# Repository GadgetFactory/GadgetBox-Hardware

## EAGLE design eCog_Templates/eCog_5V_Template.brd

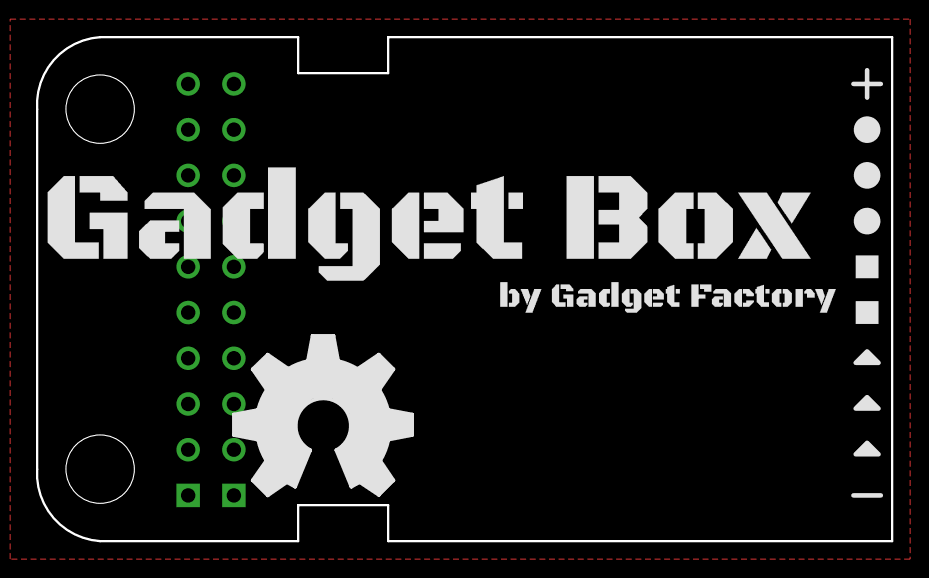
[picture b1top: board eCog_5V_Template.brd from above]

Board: 2 copper layers, 47.5 x 28.0 mm, 11 parts (0 on the bottom side), 2 nets, no tracks yet.

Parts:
ECOG: ECOG_DUALTHROUGHHOLE; ECOG_DUAL_TH
U$1: GADGETBOX_TEXT
U$2, U$3, U$4: LEGEND_DIO
U$5, U$6: LEGEND_PWM
U$7, U$8, U$9: LEGEND_ANALOG
U$10: OSHW_FILLX350_NOTEXT

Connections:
3V3: ECOG.3V3, ECOG.3V3@B10
GND: ECOG.GND, ECOG.GND@B0

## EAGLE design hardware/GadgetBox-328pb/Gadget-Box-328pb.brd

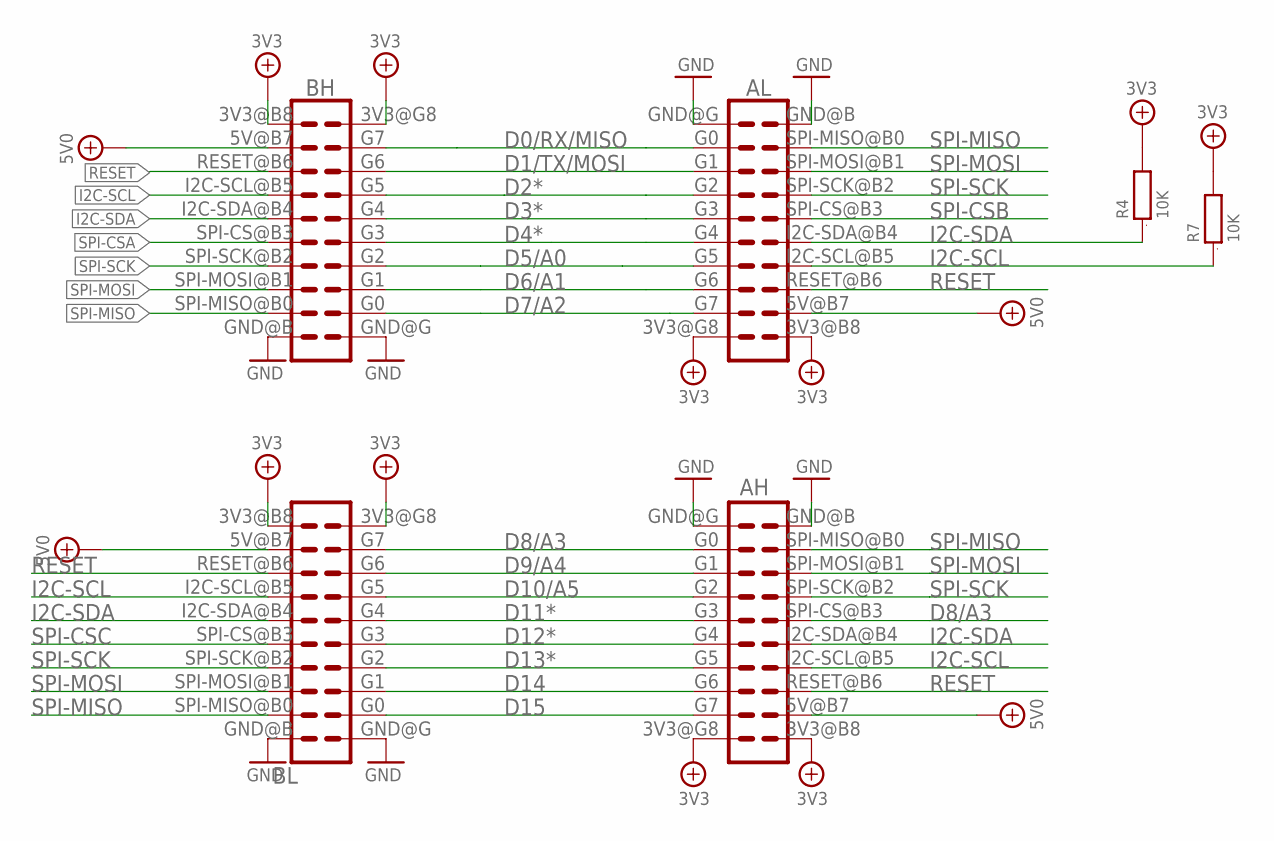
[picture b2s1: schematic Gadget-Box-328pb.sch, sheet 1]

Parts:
AH: ECOGECOG_SLOT; ECOG; PARTNO PPPC102LFBN-RC,SULLINS CONNECTOR SOLUTI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
AL: ECOGECOG_SLOT; ECOG; PARTNO PPPC102LFBN-RC,SULLINS CONNECTOR SOLUTI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
BH: ECOGECOG_SLOT; ECOG; PARTNO PPPC102LFBN-RC,SULLINS CONNECTOR SOLUTI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
BL: ECOGECOG_SLOT; ECOG; PARTNO PPPC102LFBN-RC,SULLINS CONNECTOR SOLUTI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
R4, R7: 10K; 0603; PARTNO RC0603JR-0710KL,YAGEO (VA),dk,311-10KGR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

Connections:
3V3: AH.3V3@B8 (3V3), AH.3V3@G8 (3V3), AL.3V3@B8 (3V3), AL.3V3@G8 (3V3), BH.3V3@B8 (3V3), BH.3V3@G8 (3V3), BL.3V3@B8 (3V3), BL.3V3@G8 (3V3), R4.2, R7.2; also elsewhere on the board
5V0: AH.5V@B7 (5V), AL.5V@B7 (5V), BH.5V@B7 (5V), BL.5V@B7 (5V); also elsewhere on the board
D0/RX/MISO: AL.G0, BH.G7; also elsewhere on the board
D1/TX/MOSI: AL.G1, BH.G6; also elsewhere on the board
D2*: AL.G2, BH.G5; also elsewhere on the board
D3*: AL.G3, BH.G4; also elsewhere on the board
D4*: AL.G4, BH.G3; also elsewhere on the board
D5/A0: AL.G5, BH.G2; also elsewhere on the board
D6/A1: AL.G6, BH.G1; also elsewhere on the board
D7/A2: AL.G7, BH.G0; also elsewhere on the board
D8/A3: AH.G0, AH.SPI-CS@B3 (SPI-CS), BL.G7; also elsewhere on the board
D9/A4: AH.G1, BL.G6; also elsewhere on the board
D10/A5: AH.G2, BL.G5; also elsewhere on the board
D11*: AH.G3, BL.G4; also elsewhere on the board
D12*: AH.G4, BL.G3; also elsewhere on the board
D13*: AH.G5, BL.G2; also elsewhere on the board
D14: AH.G6, BL.G1; also elsewhere on the board
D15: AH.G7, BL.G0; also elsewhere on the board
GND: AH.GND@B (GND), AH.GND@G (GND), AL.GND@B (GND), AL.GND@G (GND), BH.GND@B (GND), BH.GND@G (GND), BL.GND@B (GND), BL.GND@G (GND); also elsewhere on the board
I2C-SCL: AH.I2C-SCL@B5 (I2C-SCL), AL.I2C-SCL@B5 (I2C-SCL), BH.I2C-SCL@B5 (I2C-SCL), BL.I2C-SCL@B5 (I2C-SCL), R7.1; also elsewhere on the board
I2C-SDA: AH.I2C-SDA@B4 (I2C-SDA), AL.I2C-SDA@B4 (I2C-SDA), BH.I2C-SDA@B4 (I2C-SDA), BL.I2C-SDA@B4 (I2C-SDA), R4.1; also elsewhere on the board
RESET: AH.RESET@B6 (RESET), AL.RESET@B6 (RESET), BH.RESET@B6 (RESET), BL.RESET@B6 (RESET); also elsewhere on the board
SPI-CSA: BH.SPI-CS@B3 (SPI-CS); also elsewhere on the board
SPI-CSB: AL.SPI-CS@B3 (SPI-CS); also elsewhere on the board
SPI-CSC: BL.SPI-CS@B3 (SPI-CS); also elsewhere on the board
SPI-MISO: AH.SPI-MISO@B0 (SPI-MISO), AL.SPI-MISO@B0 (SPI-MISO), BH.SPI-MISO@B0 (SPI-MISO), BL.SPI-MISO@B0 (SPI-MISO); also elsewhere on the board
SPI-MOSI: AH.SPI-MOSI@B1 (SPI-MOSI), AL.SPI-MOSI@B1 (SPI-MOSI), BH.SPI-MOSI@B1 (SPI-MOSI), BL.SPI-MOSI@B1 (SPI-MOSI); also elsewhere on the board
SPI-SCK: AH.SPI-SCK@B2 (SPI-SCK), AL.SPI-SCK@B2 (SPI-SCK), BH.SPI-SCK@B2 (SPI-SCK), BL.SPI-SCK@B2 (SPI-SCK); also elsewhere on the board

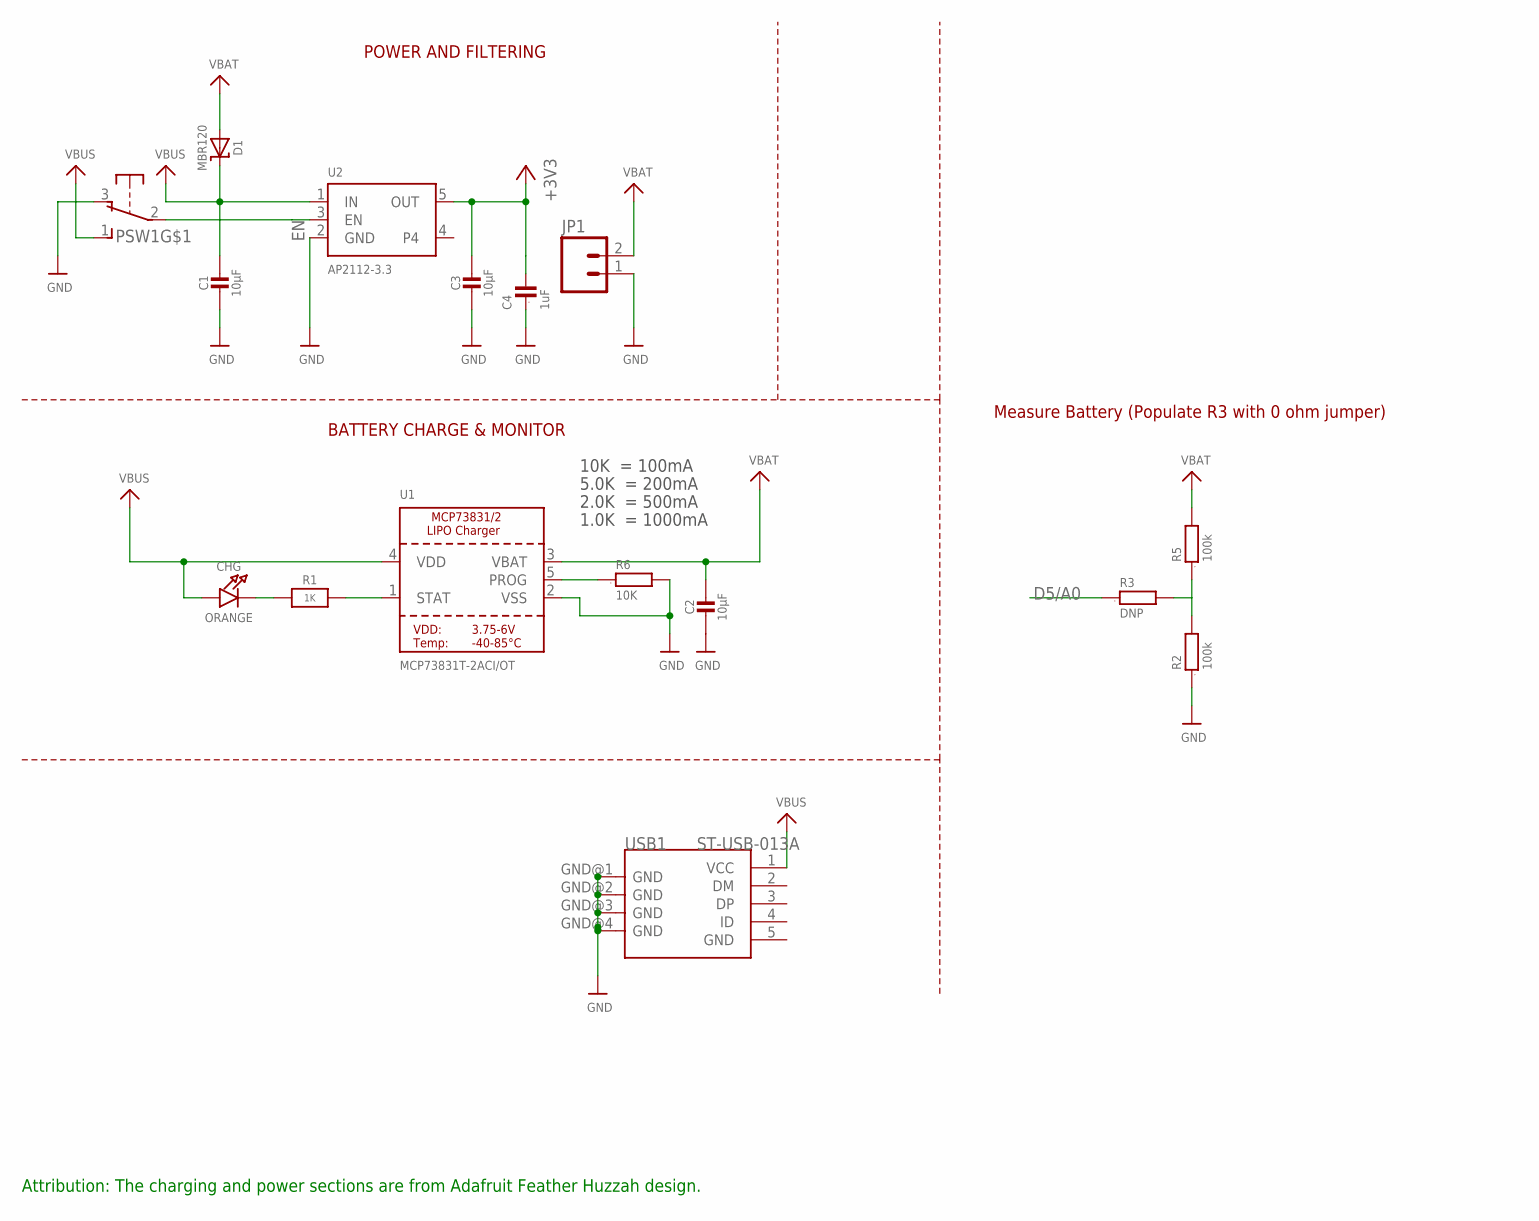
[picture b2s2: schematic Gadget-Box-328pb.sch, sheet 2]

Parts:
C1, C2, C3: 10µF; 0805-NO; PARTNO CL21F106ZPFNNNE,Samsung,DK,1276-3012-1-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
C4: 1uF; 0603; PARTNO C1608X5R1A105K080AC,TDK CORPORATION (VA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
CHG: ORANGE; CHIPLED_0805_NOOUTLINE; PARTNO LTST-C171EKT,LITE-ON INC (VA),DK,160-14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
D1: MBR120; SOD-123; PARTNO MBR120VLSFT3G,on semiconductor,dk,MBR12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
JP1: M02-JST-2-PTH-NO_SILK; JST-2-PTH-NS; PARTNO B2B-PH-SM4-TB(LF)(SN),JST SALES AMERICA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
PSW1: OS102011MA1Q; PARTNO OS102011MA1QN1,C&K Components,dk,CKN955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
R1: 1K; 0603-NO; PARTNO RC0603JR-071KL,YAGEO (VA),dk,311-1.0KGR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
R2, R5: 100k; 0603; PARTNO RC0603JR-07100KL,YAGEO (VA),dk,311-100K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
R3: DNP; 0603
R6: 10K; 0603; PARTNO RC0603JR-0710KL,YAGEO (VA),dk,311-10KGR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
U1: MCP73831T-2ACI/OT; SOT23-5; PARTNO MCP73831T-2ACI/OT,MICROCHIP TECHNOLOGY 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
U2: AP2112-3.3; SOT23-5; PARTNO AP2112K-3.3TRG1,Diodes Incorporated,dk,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
USB1: ST-USB-013A; MINIUSB5+4P-0.8-90D

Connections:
3V3: C3.1, C4.2, U2.5 (OUT); also elsewhere on the board
5V0: C1.1, CHG.A, D1.C, PSW1.1 (S), U1.4 (VDD), U2.1 (IN), USB1.1 (VCC); also elsewhere on the board
D5/A0: R3.1; also elsewhere on the board
EN: PSW1.2, U2.3 (EN)
GND: C1.2, C2.2, C3.2, C4.1, JP1.1, PSW1.3 (O), R2.1, R6.2, U1.2 (VSS), U2.2 (GND), USB1.GND@1 (GND), USB1.GND@2 (GND), USB1.GND@3 (GND), USB1.GND@4 (GND); also elsewhere on the board
unnamed: CHG.C, R1.1
unnamed: R2.2, R3.2, R5.1
unnamed: R1.2, U1.1 (STAT)
unnamed: R6.1, U1.5 (PROG)
VBAT: C2.1, D1.A, JP1.2, R5.2, U1.3 (VBAT)

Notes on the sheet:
POWER AND FILTERING
10K = 100mA
5.0K = 200mA
2.0K = 500mA
1.0K = 1000mA
BATTERY CHARGE & MONITOR
Measure Battery (Populate R3 with 0 ohm jumper)
Attribution: The charging and power sections are from Adafruit Feather Huzzah design.

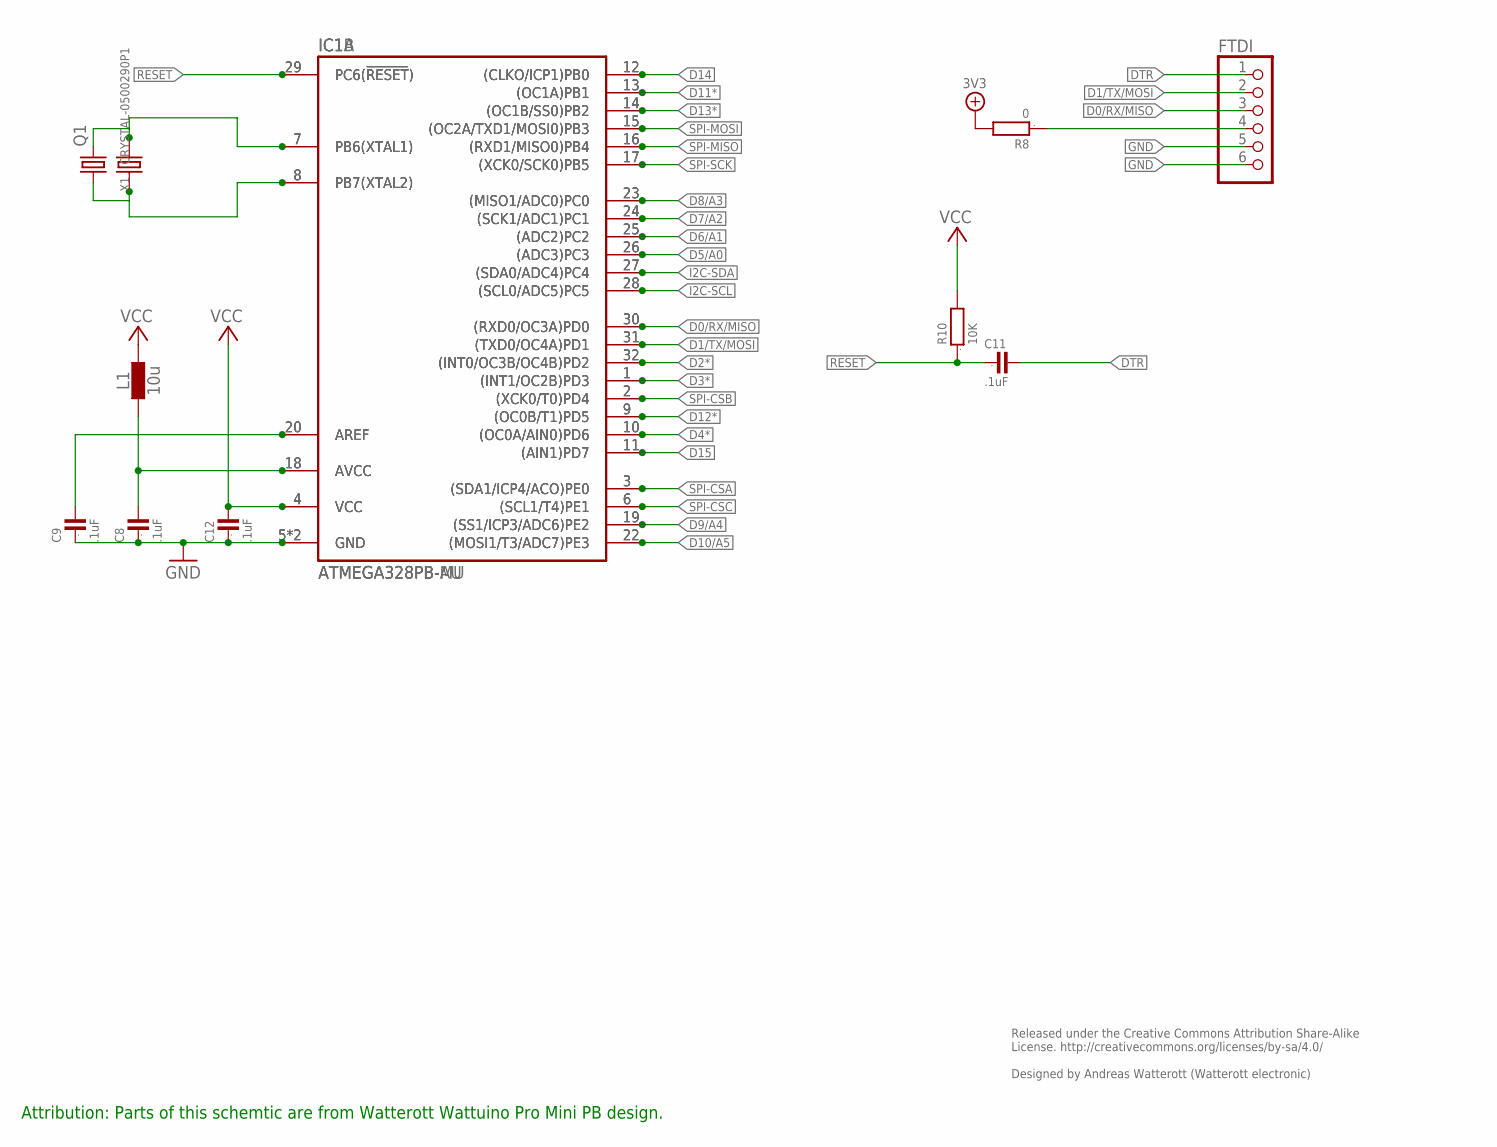
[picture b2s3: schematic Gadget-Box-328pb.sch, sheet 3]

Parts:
C8, C9, C11, C12: .1uF; 0805; PARTNO GRM21BR71E104KA01L,MURATA ELECTRONICS (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
FTDI: PINHD-1X6; 1X06; PARTNO PPPC061LGBN-RC,SULLINS CONNECTOR SOLUTI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
IC1A: ATMEGA328PB-AU; TQFP32; PARTNO ATMEGA328PB-AUR,ATMEL (VA),dk,ATMEGA328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
IC1B: ATMEGA328PB-MU; QFN32-PAD
L1: 10u; C0603; PARTNO MLZ1608E100M,TDK CORPORATION (VA),dk,44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
Q1: CRYSTALSM49; SM49; PARTNO ABLS-8.000MHZ-B4-T,Abracon Corporation,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
R8: 0; 0603
R10: 10K; 0603; PARTNO RC0603JR-0710KL,YAGEO (VA),dk,311-10KGR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
X1: CRYSTAL-0500290P1; 2P-SMD-5.0X3.2; PARTNO ABM3-8.000MHZ-D2Y-T,Abracon Corporation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

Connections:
3V3: C12.2, IC1A.4 (VCC), IC1B.4 (VCC), L1.2, R8.2, R10.2; also elsewhere on the board
AREF: C9.2, IC1A.20 (AREF), IC1B.20 (AREF)
AVCC: C8.2, IC1A.18 (AVCC), IC1B.18 (AVCC), L1.1
D0/RX/MISO: FTDI.3, IC1A.30 ((RXD0/OC3A)PD0), IC1B.30 ((RXD0/OC3A)PD0); also elsewhere on the board
D1/TX/MOSI: FTDI.2, IC1A.31 ((TXD0/OC4A)PD1), IC1B.31 ((TXD0/OC4A)PD1); also elsewhere on the board
D2*: IC1A.32 ((INT0/OC3B/OC4B)PD2), IC1B.32 ((INT0/OC3B/OC4B)PD2); also elsewhere on the board
D3*: IC1A.1 ((INT1/OC2B)PD3), IC1B.1 ((INT1/OC2B)PD3); also elsewhere on the board
D4*: IC1A.10 ((OC0A/AIN0)PD6), IC1B.10 ((OC0A/AIN0)PD6); also elsewhere on the board
D5/A0: IC1A.26 ((ADC3)PC3), IC1B.26 ((ADC3)PC3); also elsewhere on the board
D6/A1: IC1A.25 ((ADC2)PC2), IC1B.25 ((ADC2)PC2); also elsewhere on the board
D7/A2: IC1A.24 ((SCK1/ADC1)PC1), IC1B.24 ((SCK1/ADC1)PC1); also elsewhere on the board
D8/A3: IC1A.23 ((MISO1/ADC0)PC0), IC1B.23 ((MISO1/ADC0)PC0); also elsewhere on the board
D9/A4: IC1A.19 ((SS1/ICP3/ADC6)PE2), IC1B.19 ((SS1/ICP3/ADC6)PE2); also elsewhere on the board
D10/A5: IC1A.22 ((MOSI1/T3/ADC7)PE3), IC1B.22 ((MOSI1/T3/ADC7)PE3); also elsewhere on the board
D11*: IC1A.13 ((OC1A)PB1), IC1B.13 ((OC1A)PB1); also elsewhere on the board
D12*: IC1A.9 ((OC0B/T1)PD5), IC1B.9 ((OC0B/T1)PD5); also elsewhere on the board
D13*: IC1A.14 ((OC1B/SS0)PB2), IC1B.14 ((OC1B/SS0)PB2); also elsewhere on the board
D14: IC1A.12 ((CLKO/ICP1)PB0), IC1B.12 ((CLKO/ICP1)PB0); also elsewhere on the board
D15: IC1A.11 ((AIN1)PD7), IC1B.11 ((AIN1)PD7); also elsewhere on the board
DTR: C11.2, FTDI.1
GND: C8.1, C9.1, C12.1, FTDI.5, FTDI.6, IC1A.5 (GND), IC1A.21 (GND), IC1B.5 (GND), IC1B.21 (GND); also elsewhere on the board
I2C-SCL: IC1A.28 ((SCL0/ADC5)PC5), IC1B.28 ((SCL0/ADC5)PC5); also elsewhere on the board
I2C-SDA: IC1A.27 ((SDA0/ADC4)PC4), IC1B.27 ((SDA0/ADC4)PC4); also elsewhere on the board
unnamed: IC1A.8 (PB7(XTAL2)), IC1B.8 (PB7(XTAL2)), Q1.1, X1.1
unnamed: IC1A.7 (PB6(XTAL1)), IC1B.7 (PB6(XTAL1)), Q1.2, X1.2
unnamed: FTDI.4, R8.1
RESET: C11.1, IC1A.29 (PC6(!RESET!)), IC1B.29 (PC6(!RESET!)), R10.1; also elsewhere on the board
SPI-CSA: IC1A.3 ((SDA1/ICP4/ACO)PE0), IC1B.3 ((SDA1/ICP4/ACO)PE0); also elsewhere on the board
SPI-CSB: IC1A.2 ((XCK0/T0)PD4), IC1B.2 ((XCK0/T0)PD4); also elsewhere on the board
SPI-CSC: IC1A.6 ((SCL1/T4)PE1), IC1B.6 ((SCL1/T4)PE1); also elsewhere on the board
SPI-MISO: IC1A.16 ((RXD1/MISO0)PB4), IC1B.16 ((RXD1/MISO0)PB4); also elsewhere on the board
SPI-MOSI: IC1A.15 ((OC2A/TXD1/MOSI0)PB3), IC1B.15 ((OC2A/TXD1/MOSI0)PB3); also elsewhere on the board
SPI-SCK: IC1A.17 ((XCK0/SCK0)PB5), IC1B.17 ((XCK0/SCK0)PB5); also elsewhere on the board

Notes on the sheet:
Released under the Creative Commons Attribution Share-Alike License. http://creativecommons.org/licenses/by-sa/4.0/ Designed by Andreas Watterott (Watterott electronic)
Attribution: Parts of this schemtic are from Watterott Wattuino Pro Mini PB design.

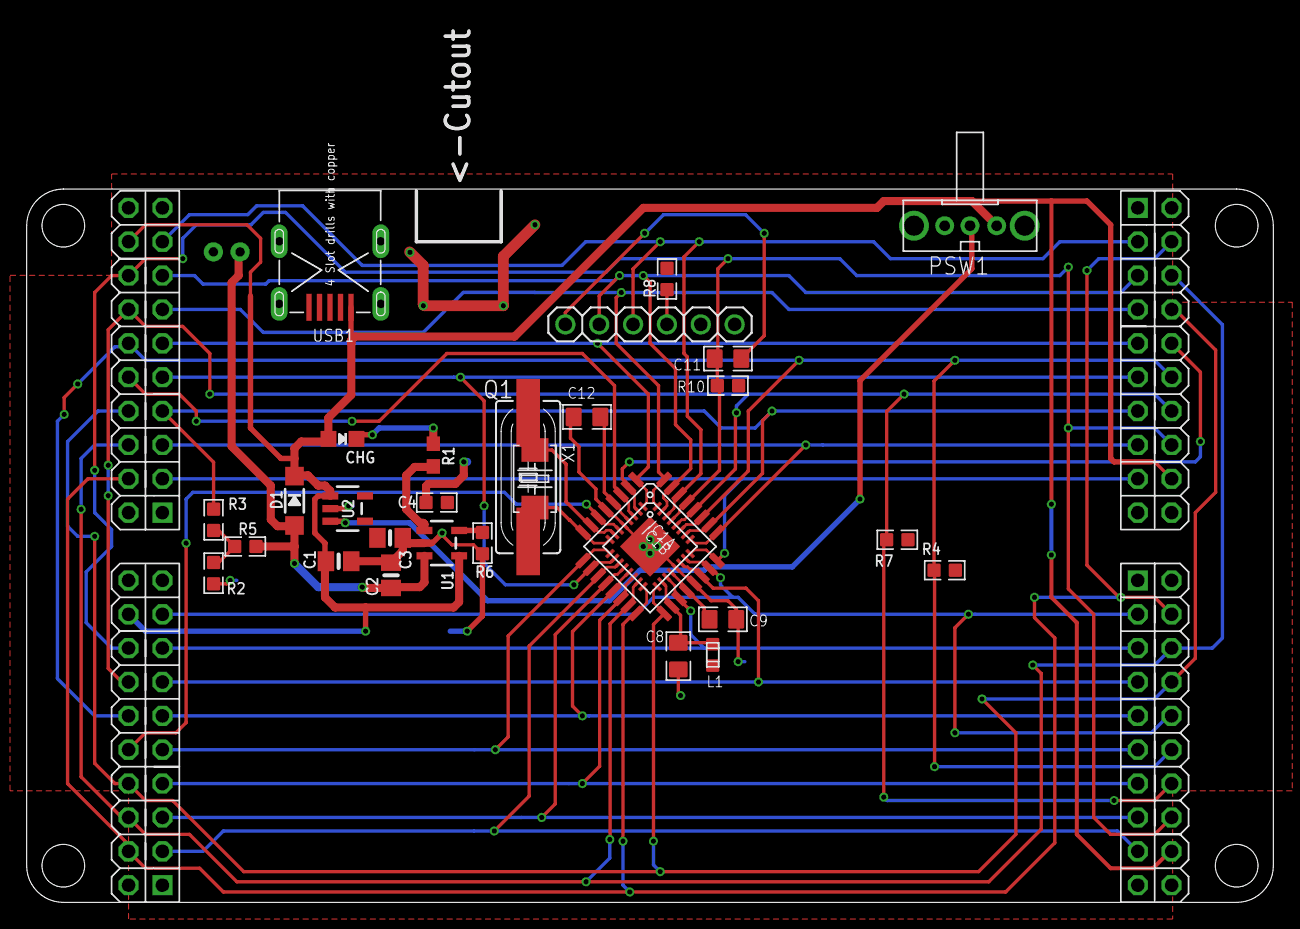
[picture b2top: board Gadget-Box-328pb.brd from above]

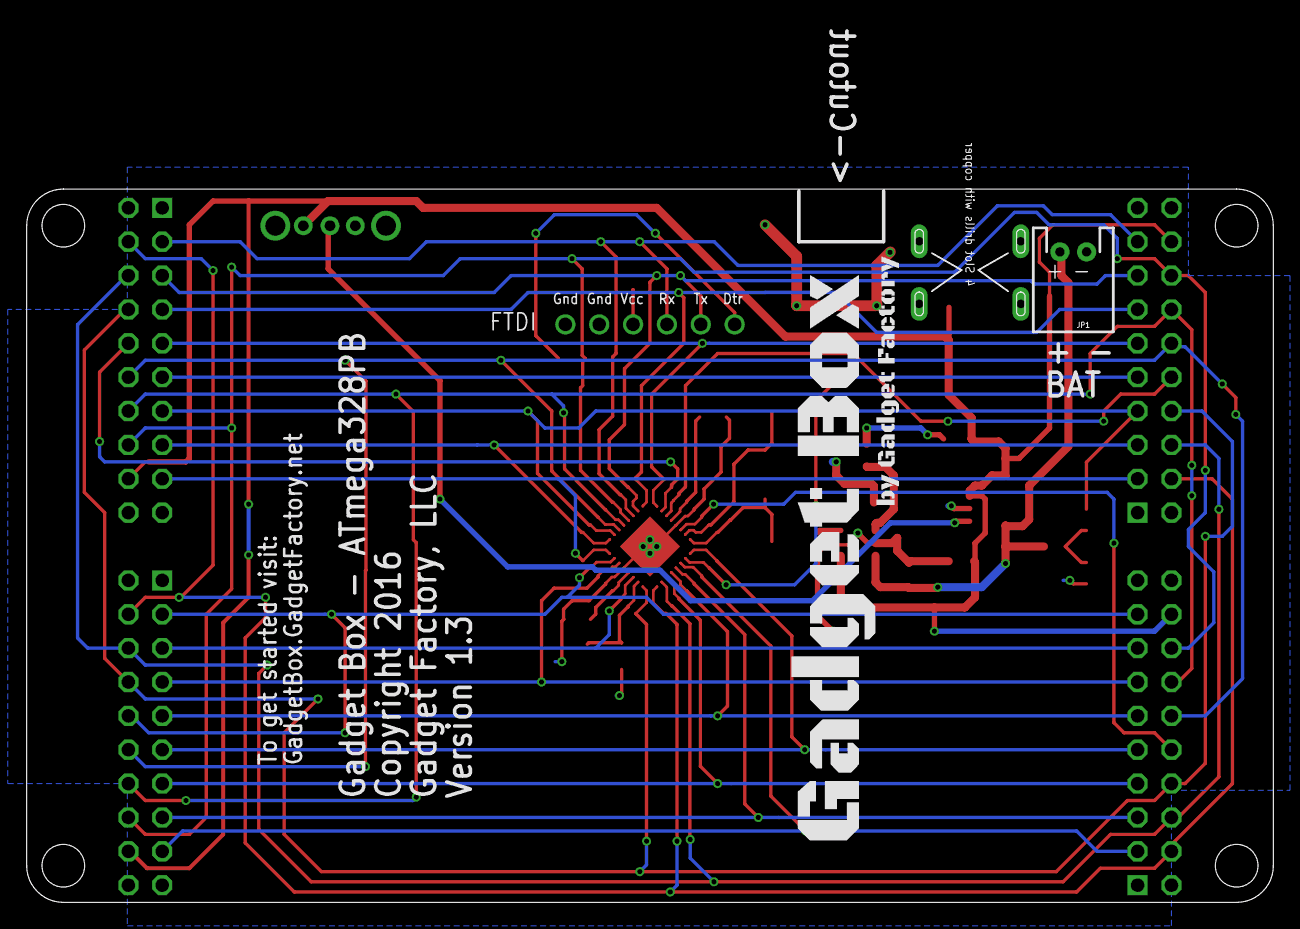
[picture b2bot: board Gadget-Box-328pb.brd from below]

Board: 2 copper layers, 93.5 x 53.5 mm, 36 parts (2 on the bottom side), 40 nets.

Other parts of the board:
$$U$1: ECOG93P53P5
U$100: GADGETBOX_TEXT

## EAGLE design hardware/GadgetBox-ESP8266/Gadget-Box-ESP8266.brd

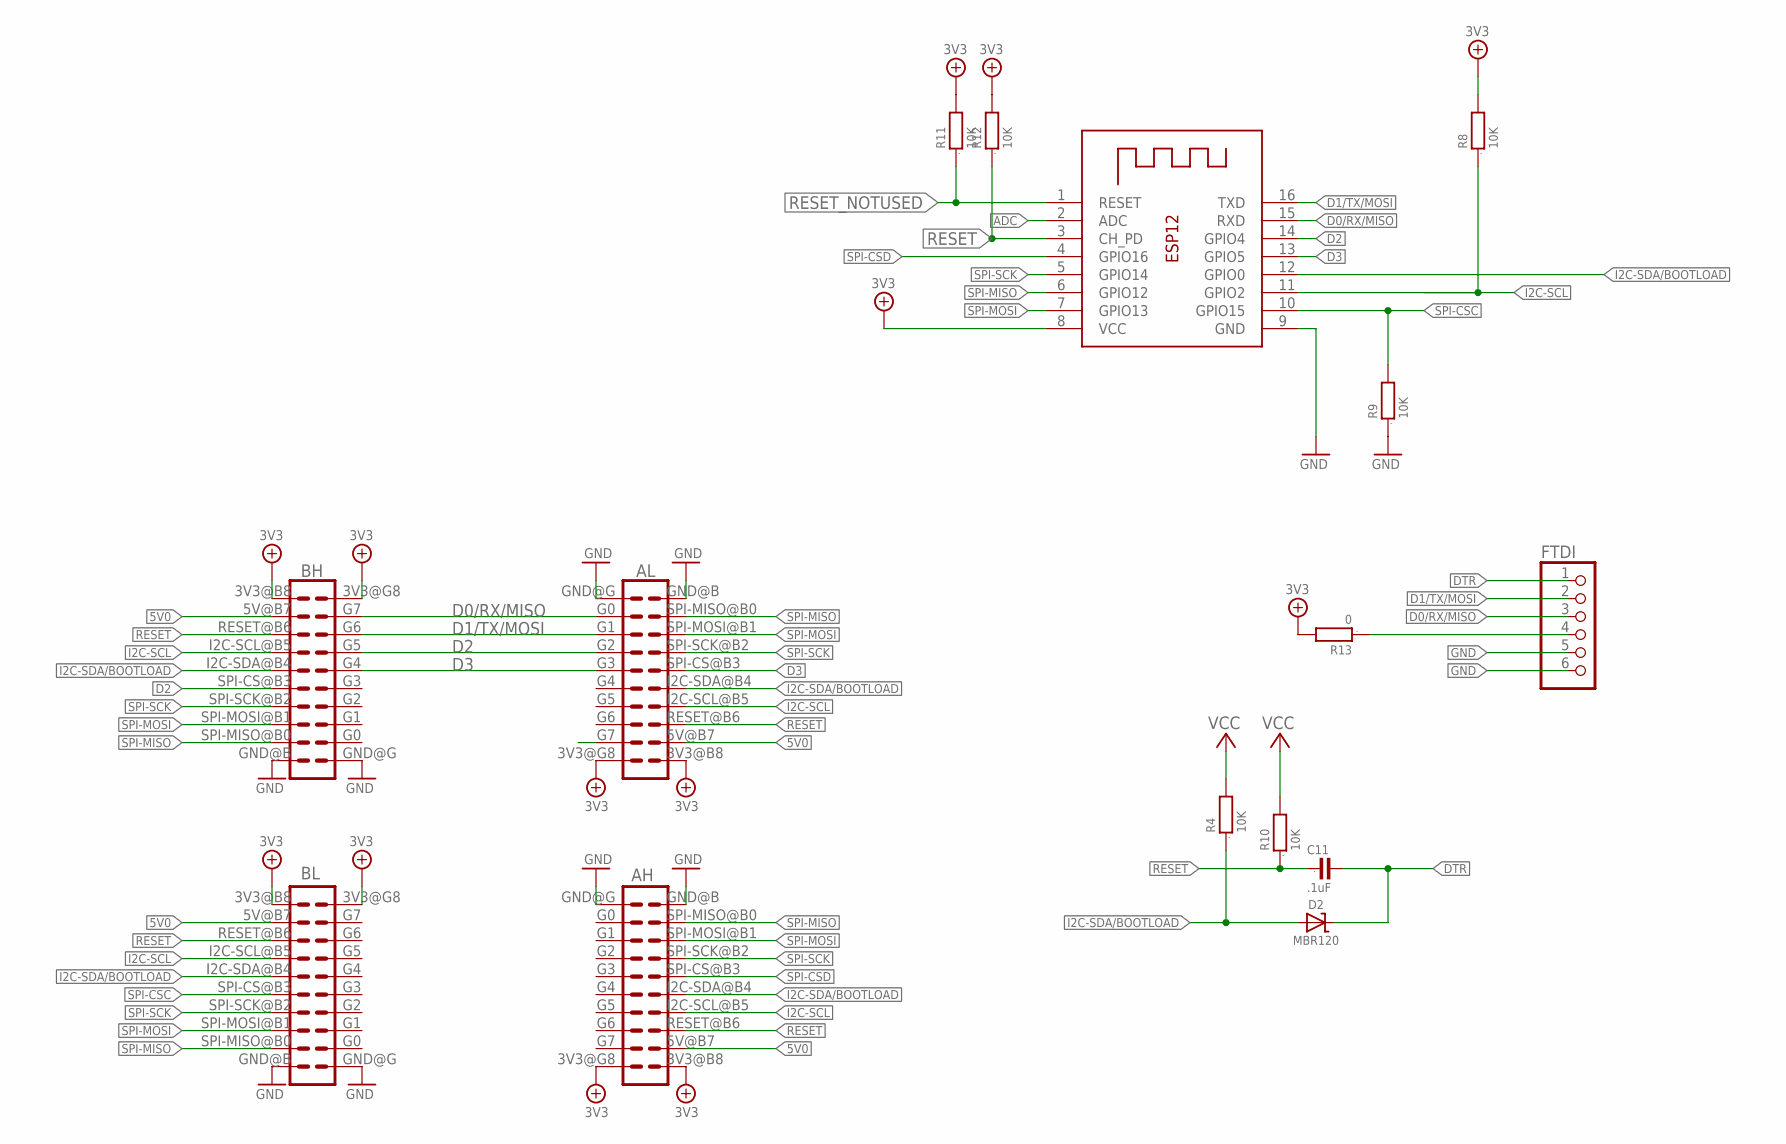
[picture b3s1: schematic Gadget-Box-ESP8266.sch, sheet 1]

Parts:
AH: ECOGECOG_SLOT; ECOG; PARTNO PPPC102LFBN-RC,SULLINS CONNECTOR SOLUTI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
AL: ECOGECOG_SLOT; ECOG; PARTNO PPPC102LFBN-RC,SULLINS CONNECTOR SOLUTI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
BH: ECOGECOG_SLOT; ECOG; PARTNO PPPC102LFBN-RC,SULLINS CONNECTOR SOLUTI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
BL: ECOGECOG_SLOT; ECOG; PARTNO PPPC102LFBN-RC,SULLINS CONNECTOR SOLUTI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
C11: .1uF; 0805; PARTNO GRM21BR71E104KA01L,MURATA ELECTRONICS (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
D2: MBR120; SOD-123; PARTNO MBR120VLSFT3G,on semiconductor,dk,MBR12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
FTDI: PINHD-1X6; 1X06; PARTNO PPPC061LGBN-RC,SULLINS CONNECTOR SOLUTI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
R4, R10: 10K; 0805; PARTNO RC0805JR-0710KL,YAGEO (VA),dk,311-10KAR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
R8, R9, R11, R12: 10K; 0805; PARTNO RC0805JR-0710KL,YAGEO (VA),dk,311-10KAR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; DIGIKEY RMCF0805JT10K0CT-ND
R13: 0; 0805
X2: ESP-12; PARTNO 385646,AI-Thinker,dx.com,385646,ESP8266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

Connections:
3V3: AH.3V3@B8 (3V3), AH.3V3@G8 (3V3), AL.3V3@B8 (3V3), AL.3V3@G8 (3V3), BH.3V3@B8 (3V3), BH.3V3@G8 (3V3), BL.3V3@B8 (3V3), BL.3V3@G8 (3V3), R8.2, R10.2, R11.2, R12.2, R13.2, X2.8 (VCC); also elsewhere on the board
5V0: AH.5V@B7 (5V), AL.5V@B7 (5V), BH.5V@B7 (5V), BL.5V@B7 (5V); also elsewhere on the board
ADC: X2.2 (ADC); also elsewhere on the board
D0/RX/MISO: AL.G0, BH.G7, FTDI.3, X2.15 (RXD)
D1/TX/MOSI: AL.G1, BH.G6, FTDI.2, X2.16 (TXD)
D2: AL.G2, BH.G5, BH.SPI-CS@B3 (SPI-CS), X2.14 (GPIO4)
D3: AL.G3, AL.SPI-CS@B3 (SPI-CS), BH.G4, X2.13 (GPIO5)
DTR: C11.2, D2.C, FTDI.1
GND: AH.GND@B (GND), AH.GND@G (GND), AL.GND@B (GND), AL.GND@G (GND), BH.GND@B (GND), BH.GND@G (GND), BL.GND@B (GND), BL.GND@G (GND), FTDI.5, FTDI.6, R9.1, X2.9 (GND); also elsewhere on the board
I2C-SCL: AH.I2C-SCL@B5 (I2C-SCL), AL.I2C-SCL@B5 (I2C-SCL), BH.I2C-SCL@B5 (I2C-SCL), BL.I2C-SCL@B5 (I2C-SCL), R8.1, X2.11 (GPIO2)
I2C-SDA/BOOTLOAD: AH.I2C-SDA@B4 (I2C-SDA), AL.I2C-SDA@B4 (I2C-SDA), BH.I2C-SDA@B4 (I2C-SDA), BL.I2C-SDA@B4 (I2C-SDA), D2.A, R4.1, X2.12 (GPIO0)
unnamed: FTDI.4, R13.1
RESET: AH.RESET@B6 (RESET), AL.RESET@B6 (RESET), BH.RESET@B6 (RESET), BL.RESET@B6 (RESET), C11.1, R10.1, R12.1, X2.3 (CH_PD)
RESET_NOTUSED: R11.1, X2.1 (RESET)
SPI-CSC: BL.SPI-CS@B3 (SPI-CS), R9.2, X2.10 (GPIO15)
SPI-CSD: AH.SPI-CS@B3 (SPI-CS), X2.4 (GPIO16)
SPI-MISO: AH.SPI-MISO@B0 (SPI-MISO), AL.SPI-MISO@B0 (SPI-MISO), BH.SPI-MISO@B0 (SPI-MISO), BL.SPI-MISO@B0 (SPI-MISO), X2.6 (GPIO12)
SPI-MOSI: AH.SPI-MOSI@B1 (SPI-MOSI), AL.SPI-MOSI@B1 (SPI-MOSI), BH.SPI-MOSI@B1 (SPI-MOSI), BL.SPI-MOSI@B1 (SPI-MOSI), X2.7 (GPIO13)
SPI-SCK: AH.SPI-SCK@B2 (SPI-SCK), AL.SPI-SCK@B2 (SPI-SCK), BH.SPI-SCK@B2 (SPI-SCK), BL.SPI-SCK@B2 (SPI-SCK), X2.5 (GPIO14)
VCC: R4.2

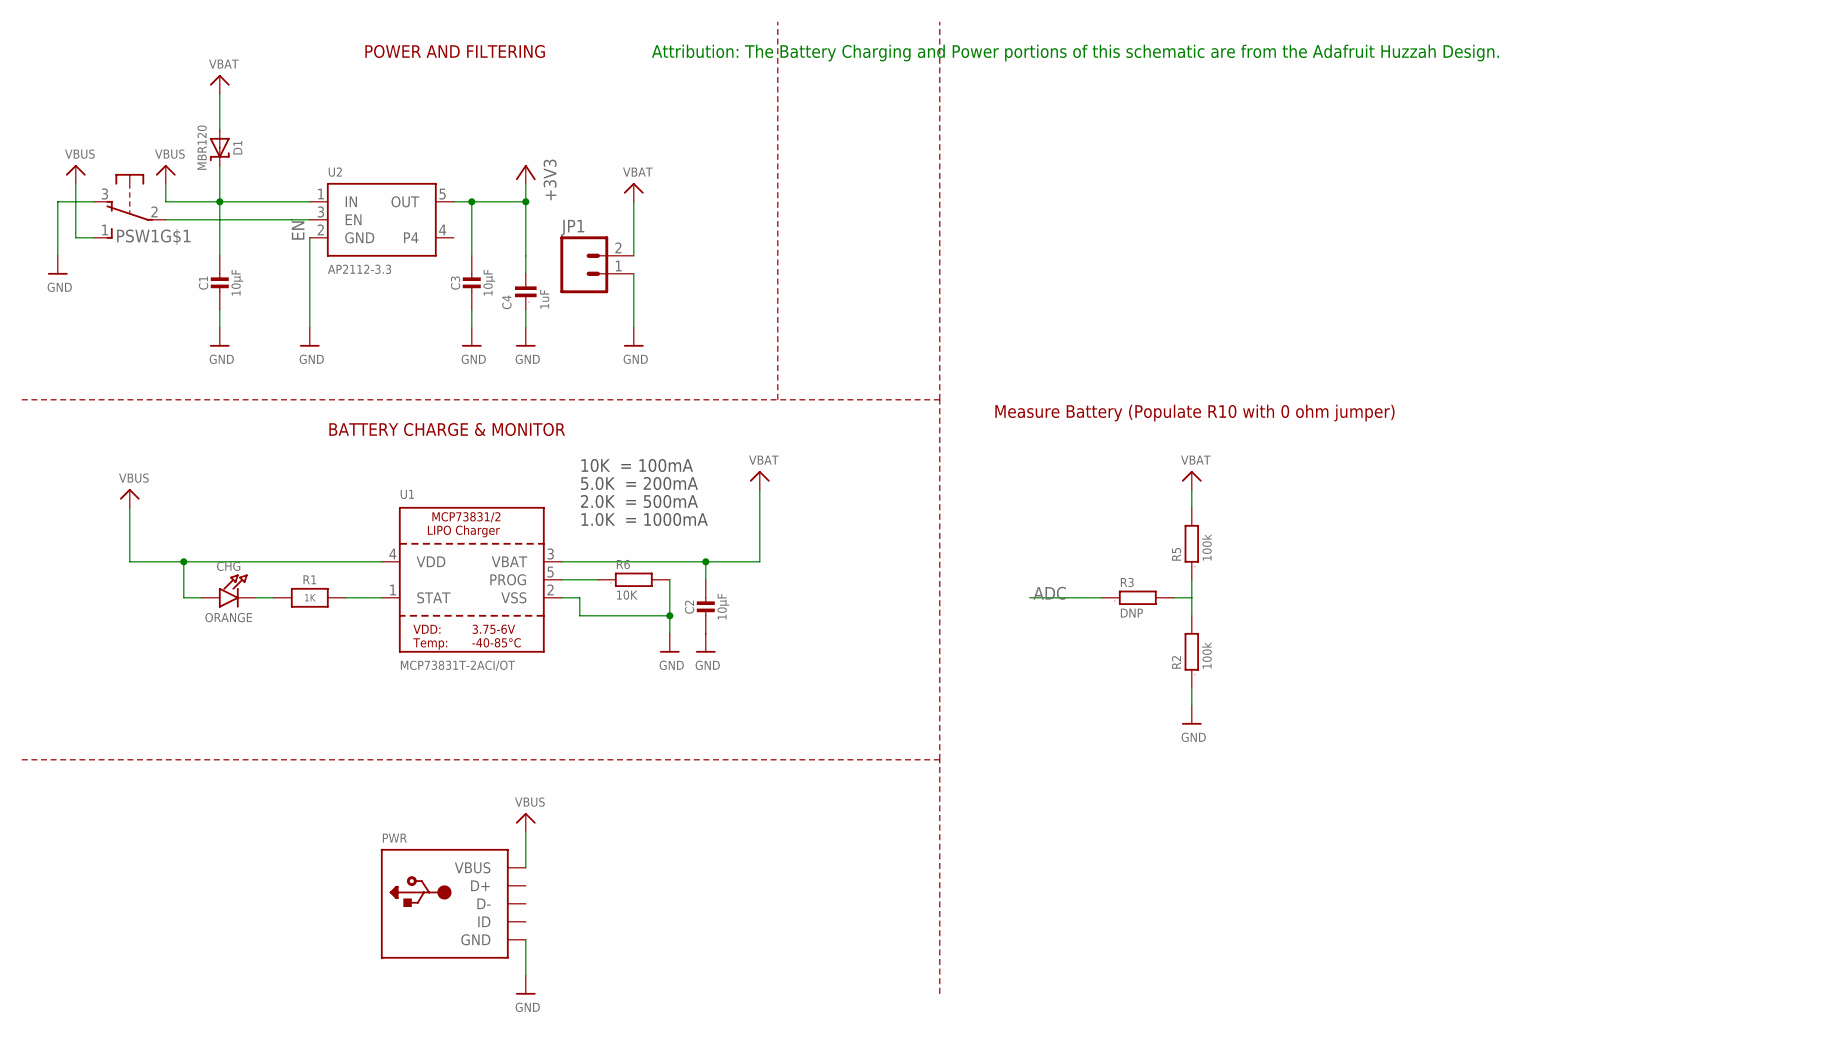
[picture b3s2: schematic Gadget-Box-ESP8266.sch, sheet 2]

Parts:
C1, C2, C3: 10µF; 0805-NO; PARTNO CL21F106ZPFNNNE,Samsung,DK,1276-3012-1-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
C4: 1uF; 0603; PARTNO C1608X5R1A105K080AC,TDK CORPORATION (VA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
CHG: ORANGE; CHIPLED_0805_NOOUTLINE; PARTNO LTST-C171EKT,LITE-ON INC (VA),DK,160-14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
D1: MBR120; SOD-123; PARTNO MBR120VLSFT3G,on semiconductor,dk,MBR12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
JP1: M02-JST-2-PTH-NO_SILK; JST-2-PTH-NS; PARTNO B2B-PH-SM4-TB(LF)(SN),JST SALES AMERICA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
PSW1: OS102011MA1Q; PARTNO OS102011MA1QN1,C&K Components,dk,CKN955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
PWR: USBMINIB; USB-MINIB; PARTNO USB-M26FTR,On Shore Technology Inc,DK,E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
R1: 1K; 0603-NO; PARTNO RC0603JR-071KL,YAGEO (VA),dk,311-1.0KGR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
R2, R5: 100k; 0603; PARTNO RC0603JR-07100KL,YAGEO (VA),dk,311-100K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
R3: DNP; 0603
R6: 10K; 0805; PARTNO RC0805JR-0710KL,YAGEO (VA),dk,311-10KAR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
U1: MCP73831T-2ACI/OT; SOT23-5; PARTNO MCP73831T-2ACI/OT,MICROCHIP TECHNOLOGY 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
U2: AP2112-3.3; SOT23-5; PARTNO AP2112K-3.3TRG1,Diodes Incorporated,dk,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

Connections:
3V3: C3.1, C4.2, U2.5 (OUT); also elsewhere on the board
5V0: C1.1, CHG.A, D1.C, PSW1.1 (S), PWR.VBUS, U1.4 (VDD), U2.1 (IN); also elsewhere on the board
ADC: R3.1; also elsewhere on the board
EN: PSW1.2, U2.3 (EN)
GND: C1.2, C2.2, C3.2, C4.1, JP1.1, PSW1.3 (O), PWR.GND, R2.1, R6.2, U1.2 (VSS), U2.2 (GND); also elsewhere on the board
unnamed: CHG.C, R1.1
unnamed: R2.2, R3.2, R5.1
unnamed: R1.2, U1.1 (STAT)
unnamed: R6.1, U1.5 (PROG)
VBAT: C2.1, D1.A, JP1.2, R5.2, U1.3 (VBAT)

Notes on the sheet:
POWER AND FILTERING
10K = 100mA
5.0K = 200mA
2.0K = 500mA
1.0K = 1000mA
BATTERY CHARGE & MONITOR
Measure Battery (Populate R10 with 0 ohm jumper)
Attribution: The Battery Charging and Power portions of this schematic are from the Adafruit Huzzah Design.

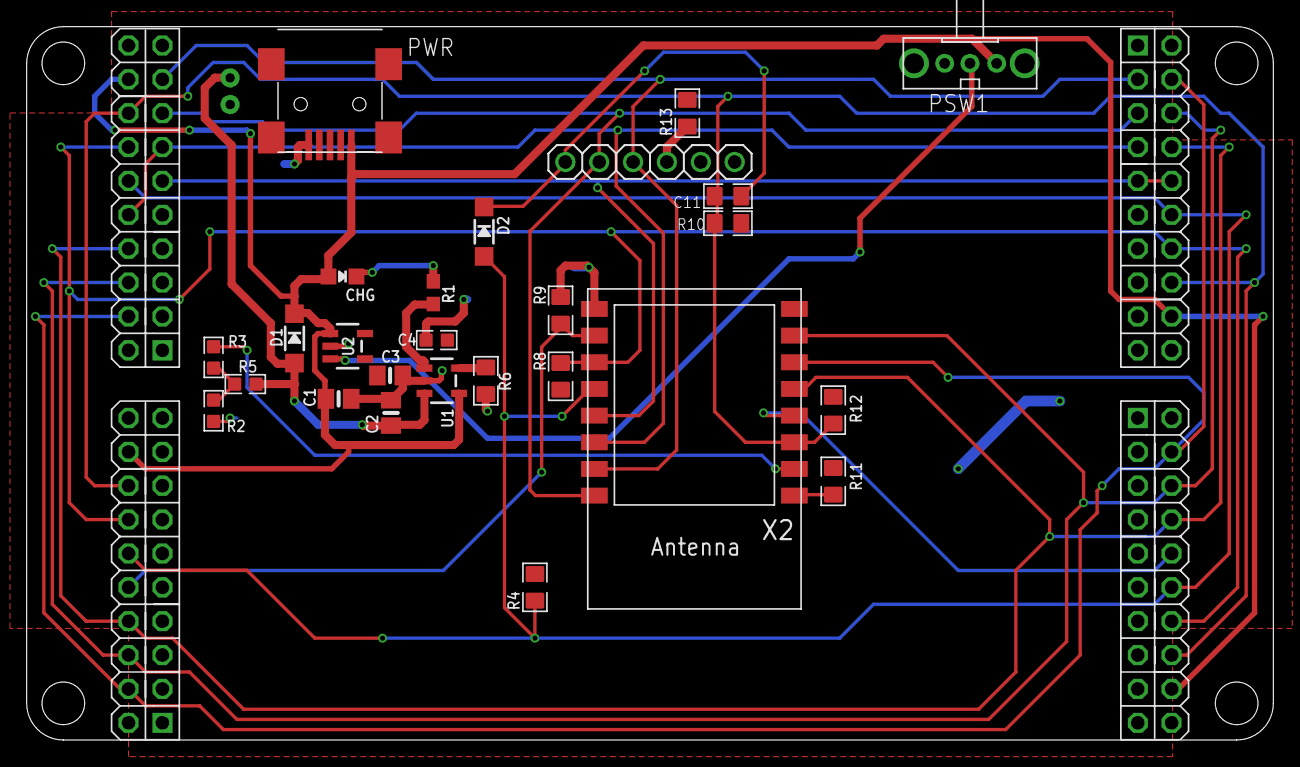
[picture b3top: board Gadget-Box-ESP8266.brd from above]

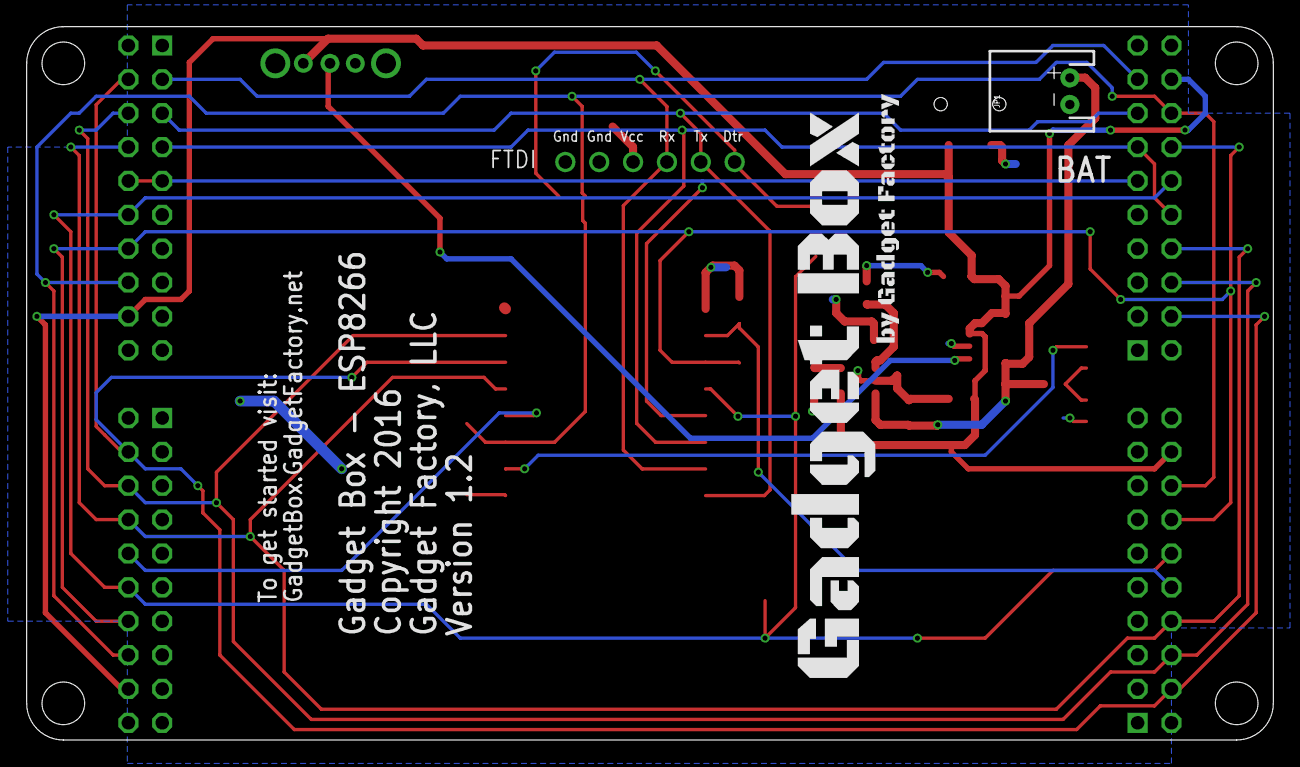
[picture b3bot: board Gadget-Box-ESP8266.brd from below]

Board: 2 copper layers, 93.5 x 53.5 mm, 33 parts (2 on the bottom side), 25 nets.

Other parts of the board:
$$U$1: ECOG93P53P5
U$100: GADGETBOX_TEXT

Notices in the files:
eCog_Templates/eCog_5V_Template.brd:
Copyright 2016
parts and their libraries:
microbuilder: This work is placed in the public domain, and may be freely used for commercial and non-commercial work with the following conditions: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
SparkFun: Licensing: CC v3.0 Share-Alike You are welcome to use this library for commercial purposes.
